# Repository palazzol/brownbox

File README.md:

# Ralph Baer's "Brown Box" prototype

## Ralph Baer created a series of [TV game prototypes](https://americanhistory.si.edu/collections/object-groups/the-father-of-the-video-game-the-ralph-baer-prototypes-and-electronic-games) in the 1960s, that led to the first commercial TV game console, the [Magnavox Odyssey](https://en.wikipedia.org/wiki/Magnavox_Odyssey). This github is for files related to the the ["Brown Box"](https://americanhistory.si.edu/collections/search/object/nmah_1301997) - the last prototype that was created and resides in the Smithsonian.

## Goals
1. We would like to create a **functional PCB version** of the Brown Box, which can be populated by modern (or vintage) transistors

1. We have reason to believe the "build to print" Brown Box, and the actual artifact, are *__somewhat different__*.  We want to understand these differences, as well as the differences between the "brown box" and the eventual manufactured Magnavox Odyssey console.

## Contents

The current KiCAD schematic and PCB layout is based on this original schematic, which is the best copy "available" on the Smithsonian website.

https://raw.githubusercontent.com/palazzol/brownbox/master/original_schems/NMAH-AC0854-0000802.jpg

### The KiCAD schematic is complete!

### The initial KiCAD PCB is finally done!

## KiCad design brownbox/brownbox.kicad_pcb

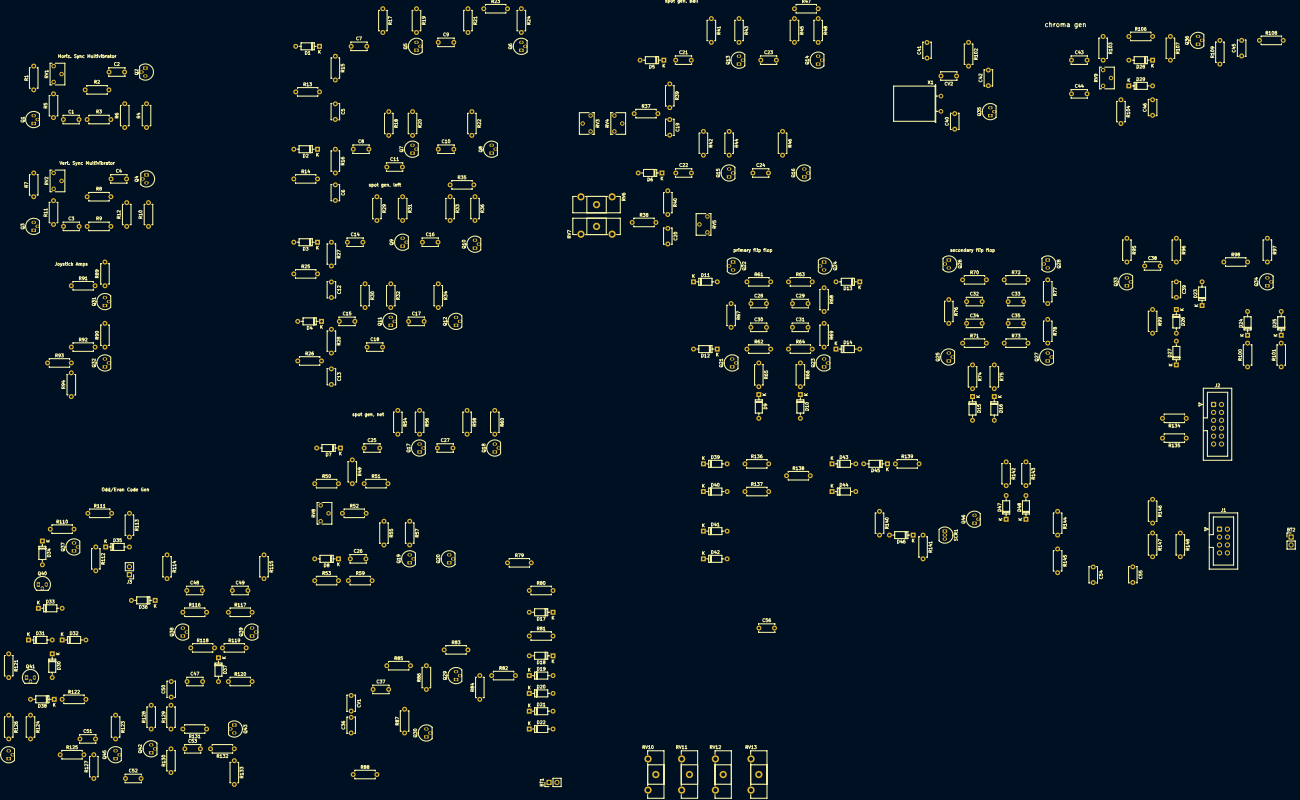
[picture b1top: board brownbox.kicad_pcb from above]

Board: 2 copper layers, 319 parts (0 on the bottom side), 160 nets, no tracks yet.

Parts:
BT1: 4 D Cells; PinHeader_1x02_P2.54mm_Vertical
BT2: 1 C Cell; PinHeader_1x02_P2.54mm_Vertical
C1: 390pF; C_Disc_D5.0mm_W2.5mm_P5.00mm
C2: 330pF; C_Disc_D5.0mm_W2.5mm_P5.00mm
C3, C8, C10, C15, C17, C22, C24, C26, C28, C29, C32, C33, C39, C47, C52, C53: 0.1uF; C_Disc_D5.0mm_W2.5mm_P5.00mm
C4: 0.2uF; C_Disc_D5.0mm_W2.5mm_P5.00mm
C5, C6, C12, C13, C19, C20: 100uF; C_Disc_D5.0mm_W2.5mm_P5.00mm
C7, C14, C21, C25: 750pF; C_Disc_D5.0mm_W2.5mm_P5.00mm
C9, C16, C23, C27: 130pF; C_Disc_D5.0mm_W2.5mm_P5.00mm
C11, C18, C41, C48, C49, C50: 0.01uF; C_Disc_D5.0mm_W2.5mm_P5.00mm
C30, C31, C34, C35: 100pF; C_Disc_D5.0mm_W2.5mm_P5.00mm
C36: 82pF; C_Disc_D5.0mm_W2.5mm_P5.00mm
C37, C43: 180pF; C_Disc_D5.0mm_W2.5mm_P5.00mm
C38: 0.22uF; C_Disc_D5.0mm_W2.5mm_P5.00mm
C40: 27pF; C_Disc_D5.0mm_W2.5mm_P5.00mm
C42: 62pF; C_Disc_D5.0mm_W2.5mm_P5.00mm
C44: 56pF; C_Disc_D5.0mm_W2.5mm_P5.00mm
C45: 360pF; C_Disc_D5.0mm_W2.5mm_P5.00mm
C46: 120pF; C_Disc_D5.0mm_W2.5mm_P5.00mm
C51: 0.3uF; C_Disc_D5.0mm_W2.5mm_P5.00mm
C54, C55: 10uF; C_Disc_D5.0mm_W2.5mm_P5.00mm
C56: 0.02uF; C_Disc_D5.0mm_W2.5mm_P5.00mm
CV1, CV2: 9-35pF; C_Disc_D5.0mm_W2.5mm_P5.00mm
D1, D2, D3, D4, D5, D6, D7, D8, D9, D10, D15, D16, D17, D18, D19, D20, D21, D22, D24, D25, D26, D27, D28, D29, D30, D31, D32, D33, D34, D35, D36, D37, D38, D45, D46, D47, D48: 1N4148; D_DO-35_SOD27_P7.62mm_Horizontal
D11, D12, D13, D14, D23, D39, D40, D41, D42, D43, D44: 1N270; D_DO-35_SOD27_P7.62mm_Horizontal
J1: Rifle Connector - C7-205; IDC-Header_2x04_P2.54mm_Vertical
J2: 12-Pin Cinch Jones Expansion Connector; IDC-Header_2x06_P2.54mm_Vertical
J3: Jumper; PinHeader_1x02_P2.54mm_Vertical
Q1, Q3, Q5, Q6, Q8, Q9, Q10, Q12, Q13, Q14, Q16, Q17, Q18, Q20, Q29, Q30, Q35, Q36: 2N5134; TO-92_Offset_TO-106
Q2, Q4, Q22, Q24, Q26, Q28, Q40, Q41, Q43: 2N5139; TO-92_Offset_TO-106
Q7, Q11, Q15, Q19, Q21, Q23, Q25, Q27, Q31, Q32, Q33, Q34, Q37, Q38, Q39, Q42, Q44, Q45, Q46: 2N5133; TO-92_Offset_TO-106
R1, R2, R3, R4, R7, R8, R9, R10, R13, R14, R23, R25, R26, R35, R37, R38, R47, R67, R76, R85, R131, R132, R133: 2K; R_Axial_DIN0207_L6.3mm_D2.5mm_P7.62mm_Horizontal
R5, R11, R87, R148: 150K; R_Axial_DIN0207_L6.3mm_D2.5mm_P7.62mm_Horizontal
R6, R12: 220K; R_Axial_DIN0207_L6.3mm_D2.5mm_P7.62mm_Horizontal
R15, R16, R19, R20, R24, R27, R28, R31, R32, R36, R39, R40, R43, R44, R48, R49, R53, R56, R57, R60, R65, R66, R74, R75, R83, R86, R93, R95, R97, R103, R104, R110, R111, R114, R115, R120, R123, R126, R134, R135, R139, R140, R141: 10K; R_Axial_DIN0207_L6.3mm_D2.5mm_P7.62mm_Horizontal
R17, R29, R41, R54: 130K; R_Axial_DIN0207_L6.3mm_D2.5mm_P7.62mm_Horizontal
R18, R30, R42, R55: 270K; R_Axial_DIN0207_L6.3mm_D2.5mm_P7.62mm_Horizontal
R21, R33, R45, R122: 33K; R_Axial_DIN0207_L6.3mm_D2.5mm_P7.62mm_Horizontal
R22, R34, R46, R109: 15K; R_Axial_DIN0207_L6.3mm_D2.5mm_P7.62mm_Horizontal
R50, R51, R59, R79, R89, R90, R128, R129, R136, R137, R138: 5.1K; R_Axial_DIN0207_L6.3mm_D2.5mm_P7.62mm_Horizontal
R52: 220; R_Axial_DIN0207_L6.3mm_D2.5mm_P7.62mm_Horizontal
R58, R61, R62, R63, R64, R70, R71, R72, R73, R130, R142, R143: 22K; R_Axial_DIN0207_L6.3mm_D2.5mm_P7.62mm_Horizontal
R68, R69, R77, R78, R144, R145: 1K; R_Axial_DIN0207_L6.3mm_D2.5mm_P7.62mm_Horizontal
R80, R81, R98, R99, R112, R113, R116, R117, R118, R119, R124, R125: 100K; R_Axial_DIN0207_L6.3mm_D2.5mm_P7.62mm_Horizontal
R82, R94: 12K; R_Axial_DIN0207_L6.3mm_D2.5mm_P7.62mm_Horizontal
R84: 1.8K; R_Axial_DIN0207_L6.3mm_D2.5mm_P7.62mm_Horizontal
R88: 270; R_Axial_DIN0207_L6.3mm_D2.5mm_P7.62mm_Horizontal
R91, R92, R108, R121, R127: 51K; R_Axial_DIN0207_L6.3mm_D2.5mm_P7.62mm_Horizontal
R96: 510K; R_Axial_DIN0207_L6.3mm_D2.5mm_P7.62mm_Horizontal
R100, R101: 20K; R_Axial_DIN0207_L6.3mm_D2.5mm_P7.62mm_Horizontal
R102: 300K; R_Axial_DIN0207_L6.3mm_D2.5mm_P7.62mm_Horizontal
R106, R107: 6.2K; R_Axial_DIN0207_L6.3mm_D2.5mm_P7.62mm_Horizontal
R146, R147: 100; R_Axial_DIN0207_L6.3mm_D2.5mm_P7.62mm_Horizontal
RV1, RV2: 100K; Potentiometer_Bourns_3266W_Vertical
RV3, RV5, RV8: 10K; Potentiometer_Bourns_3266W_Vertical
RV4, RV9: 5K; Potentiometer_Bourns_3266W_Vertical
RV6, RV7: 25K; Potentiometer_Piher_PT-15-H01_Horizontal
RV10, RV11, RV12, RV13: 5K; Potentiometer_Piher_PT-15-H01_Horizontal
SCR1: NT854; TO-92_Inline
X1: 3.579545Mhz; Crystal_HC49-U_Horizontal

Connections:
A: D17.1 (K), Q1.3 (C), R1.1, R2.2, R80.2, R108.2
B: D18.1 (K), Q3.3 (C), R7.1, R8.2, R81.2
E: C31.1, Q21.2 (B), R64.1, R65.1, R100.1
E': C35.1, Q25.2 (B), R73.1, R74.1, R75.1
F: C30.2, Q23.2 (B), R62.2, R66.1, R101.1
F': C34.2, Q27.2 (B), R71.2
GNDREF: BT1.2 (-), C5.2, C6.2, C12.2, C13.2, C19.2, C20.2, C36.2, C40.1, C41.1, C45.1, C54.2, C55.2, CV1.2, Q1.1 (E), Q3.1 (E), Q5.1 (E), Q6.1 (E), Q7.1 (E), Q8.1 (E), Q9.1 (E), Q10.1 (E), Q11.1 (E), Q12.1 (E), Q13.1 (E), Q14.1 (E), Q15.1 (E), Q16.1 (E), Q17.1 (E), Q18.1 (E), Q19.1 (E), Q20.1 (E), Q21.1 (E), Q23.1 (E), Q25.1 (E), Q27.1 (E), Q29.1 (E), Q30.1 (E), Q31.1 (E), Q32.1 (E), Q33.1 (E), Q34.1 (E), Q35.1 (E), Q36.1 (E), Q37.1 (E), Q38.1 (E), Q39.1 (E), Q42.1 (E), Q44.1 (E), Q45.1 (E), Q46.1 (E), R4.2, R6.2, R10.2, R12.2, R50.1, R53.1, R84.1, R94.2, R99.2, R104.2, R109.1, R112.2, R120.2, R130.1, R133.2, R141.2, R145.2, R148.2, RV3.1, RV5.1, RV8.3, RV10.3, RV11.3, RV12.3, RV13.3, SCR1.3 (K)
unnamed: C1.1, Q1.2 (B), R5.2
unnamed: C1.2, R3.2
unnamed: C2.1, Q2.2 (B), R6.1
unnamed: C2.2, R2.1
unnamed: C3.1, Q3.2 (B), R11.2
unnamed: C3.2, R9.2
unnamed: C4.1, Q4.2 (B), R12.1
unnamed: C4.2, R8.1
unnamed: C5.1, R13.2, R15.2
unnamed: C6.1, R14.2, R16.2
unnamed: C7.1, D1.1 (K), R15.1
unnamed: C7.2, Q5.2 (B), R17.2
unnamed: C8.2, Q7.2 (B), R18.2
unnamed: C9.1, Q5.3 (C), R19.2
unnamed: C9.2, Q6.2 (B), R21.2
unnamed: C10.1, Q7.3 (C), R20.2
unnamed: C10.2, C11.2, Q8.2 (B), R22.2
unnamed: C8.1, C11.1, D2.1 (K), R16.1
unnamed: C12.1, R25.2, R27.2
unnamed: C13.1, R26.2, R28.2
unnamed: C14.1, D3.1 (K), R27.1
unnamed: C14.2, Q9.2 (B), R29.2
unnamed: C15.1, C18.1, D4.1 (K), R28.1
unnamed: C15.2, Q11.2 (B), R30.2
unnamed: C16.1, Q9.3 (C), R31.2
unnamed: C16.2, Q10.2 (B), R33.2
unnamed: C17.1, Q11.3 (C), R32.2
unnamed: C17.2, C18.2, Q12.2 (B), R34.2
unnamed: C19.1, R37.2, R39.2
unnamed: C20.1, R38.2, R40.2
unnamed: C21.2, Q13.2 (B), R41.2
unnamed: C22.2, Q15.2 (B), R42.2
unnamed: C23.1, Q13.3 (C), R43.2
unnamed: C23.2, Q14.2 (B), R45.2
unnamed: C24.1, Q15.3 (C), R44.2
unnamed: C24.2, Q16.2 (B), R46.2
unnamed: C25.1, D7.1 (K), R49.1
unnamed: C25.2, Q17.2 (B), R54.2
unnamed: C26.1, D8.1 (K), R53.2, R59.1
unnamed: C26.2, Q19.2 (B), R55.2
unnamed: C27.1, Q17.3 (C), R56.2
unnamed: C27.2, Q18.2 (B), R58.2
unnamed: C28.1, D11.2 (A), Q22.3 (C), R61.1, R67.1
unnamed: C28.2, Q24.2 (B), R61.2
unnamed: C29.1, Q22.2 (B), R63.1
unnamed: C29.2, D13.2 (A), Q24.3 (C), R63.2, R68.1
unnamed: C30.1, D12.1 (K), Q21.3 (C), R62.1, R67.2
unnamed: C31.2, D14.1 (K), Q23.3 (C), R64.2, R69.2
unnamed: C32.1, Q26.3 (C), R70.1, R76.1
unnamed: C32.2, Q28.2 (B), R70.2
unnamed: C33.1, Q26.2 (B), R72.1
unnamed: C33.2, Q28.3 (C), R72.2, R77.1
unnamed: C34.1, Q25.3 (C), R71.1, R76.2
unnamed: C35.2, Q27.3 (C), R73.2, R78.2
unnamed: C36.1, Q30.2 (B), R87.1
unnamed: C37.1, CV1.1
unnamed: C37.2, Q30.3 (C), R86.1, R87.2
unnamed: C38.1, Q33.3 (C), R95.2
unnamed: C38.2, D23.2 (A), Q34.2 (B), R96.2
unnamed: C39.1, Q33.2 (B), R98.1
unnamed: C39.2, D26.1 (K), R99.1
unnamed: C40.2, Q35.2 (B), R102.2, X1.2
unnamed: C42.1, CV2.1, Q35.3 (C)
unnamed: C43.2, D28.2 (A), R103.2, R104.1, RV9.1
unnamed: C44.2, D29.1 (K), RV9.2, RV9.3
unnamed: C45.2, Q36.2 (B), R108.1, R109.2
unnamed: C46.2, D28.1 (K), D29.2 (A), R107.2
unnamed: C47.1, C50.2, D33.2 (A), Q40.3 (C)
unnamed: C47.2, D37.2 (A), R120.1
unnamed: C48.1, D36.1 (K), Q38.3 (C), R114.2, R116.1
unnamed: C48.2, Q39.2 (B), R116.2, R119.2
unnamed: C49.1, Q38.2 (B), R117.1, R118.1
unnamed: C49.2, C52.2, Q39.3 (C), R115.2, R117.2
unnamed: C50.1, R129.2
unnamed: C51.1, Q44.2 (B)
unnamed: C51.2, Q45.3 (C), R122.2, R123.2
unnamed: C52.1, R127.1
unnamed: C53.1, Q42.2 (B), R129.1, R130.2
unnamed: C53.2, R132.2
unnamed: CV2.2, X1.1
unnamed: D1.2 (A), D3.2 (A), D5.2 (A), D7.2 (A), Q2.3 (C), R3.1, R4.1
unnamed: D9.1 (K), R65.2
unnamed: D10.1 (K), R66.2
unnamed: D15.1 (K), R74.2
unnamed: D16.1 (K), R75.2
unnamed: D17.2 (A), D18.2 (A), D19.1 (K), D20.1 (K), D21.1 (K), D22.1 (K), R82.2
unnamed: D21.2 (A), D42.1 (K), Q10.3 (C), Q12.3 (C), R36.2
unnamed: D22.2 (A), D41.1 (K), Q6.3 (C), Q8.3 (C), R24.2
unnamed: D24.1 (K), R100.2
unnamed: D24.2 (A), D25.2 (A), Q34.3 (C), R97.2, R98.2
unnamed: D25.1 (K), R101.2
unnamed: D30.2 (A), Q41.3 (C)
unnamed: D34.1 (K), R110.1
unnamed: D34.2 (A), Q40.2 (B)
unnamed: D35.1 (K), Q37.2 (B), R112.1
unnamed: D35.2 (A), J3.2, R113.2
unnamed: D36.2 (A), J3.1
unnamed: D37.1 (K), R118.2, R119.1
unnamed: D38.1 (K), R122.1
unnamed: D38.2 (A), Q41.2 (B), R121.2
unnamed: D43.2 (A), D44.2 (A), D45.2 (A), R138.2
unnamed: D45.1 (K), R139.1
unnamed: D47.1 (K), D48.1 (K), Q46.2 (B)
unnamed: D47.2 (A), R142.2
unnamed: D48.2 (A), R143.2
unnamed: Q19.3 (C), Q20.2 (B), R57.2
unnamed: Q29.2 (B), R79.1, R80.1, R81.1, R82.1, R83.2, R84.2
unnamed: Q29.3 (C), R83.1, R85.2, R86.2
unnamed: Q32.2 (B), R92.1, R93.2, R94.1
unnamed: Q36.3 (C), R106.2, R107.1
unnamed: Q37.3 (C), R110.2, R111.1
unnamed: Q42.3 (C), R128.1, R131.2
unnamed: Q43.2 (B), R131.1
unnamed: Q44.3 (C), R124.2, R125.1, R126.2
unnamed: Q45.2 (B), R125.2, R127.2
unnamed: R5.1, RV1.2, RV1.3
unnamed: R11.1, RV2.2, RV2.3
unnamed: R23.2, R24.1
unnamed: R52.1, RV8.2
S: C46.1, R79.2
S1A2: R47.2, R48.1
S1A3: R35.2, R36.1
S1B2: D19.2 (A), D44.1 (K), Q18.3 (C), R60.2
S2A3: Q31.3 (C), R89.2, R91.2
S2B3: Q32.3 (C), R90.2, R92.2
S2C2: C56.1, D26.2 (A), D27.1 (K), D27.2 (A), D46.1 (K), R141.1, SCR1.2 (G)
S2D2: Q46.3 (C), SCR1.1 (A)
S2D3: D23.1 (K), Q31.2 (B), R91.1
S3A3: D20.2 (A), D39.1 (K), D40.1 (K), D43.1 (K), Q14.3 (C), Q16.3 (C), R48.2
S4A3: R146.2, R147.1, R148.1
S7B2: RV6.2, RV7.2
S8A2: D9.2 (A), D15.2 (A), D40.2 (A), R137.1
S8A3: D46.2 (A), R140.2
S8B2: D10.2 (A), D16.2 (A), D39.2 (A), R136.1
S9A2: Q26.1 (E), Q28.1 (E)
S9B1: RV4.2, RV4.3
S9B2: R77.2, R78.1
S9B3: R68.2, R69.1
S9D1: R49.2, R50.2, R51.1
S11A3: Q43.1 (E), R111.2, R113.1, R114.1, R115.1, R123.1, R124.1, R126.1, R128.2
S11B3: D31.1 (K), D33.1 (K), Q40.1 (E), Q41.1 (E), R121.1
S11C1: D4.2 (A), D6.2 (A), D8.2 (A)
S11C2: Q4.3 (C), R9.1, R10.1
S11C3: D32.2 (A), Q43.3 (C), R132.1, R133.1
S11D3: D30.1 (K), D31.2 (A), D32.1 (K)
S12A3: C41.2, C42.2, R102.1, R103.1, R106.1
S16A1: C21.1, D5.1 (K)
S16B1: C22.1, D6.1 (K)
VCC: Q2.1 (E), Q4.1 (E), Q22.1 (E), Q24.1 (E), R1.2, R7.2, R17.1, R18.1, R19.1, R20.1, R21.1, R22.1, R23.1, R29.1, R30.1, R31.1, R32.1, R33.1, R34.1, R35.1, R41.1, R42.1, R43.1, R44.1, R45.1, R46.1, R47.1, R51.2, R54.1, R55.1, R56.1, R57.1, R58.1, R59.2, R60.1, R85.1, R89.1, R90.1, R95.1, R96.1, R97.1, R136.2, R137.2, R138.1, R142.1, R143.1, R144.1, RV1.1, RV2.1, RV3.3, RV5.3, RV8.1, RV10.1, RV11.1, RV12.1, RV13.1
a: D11.1 (K), RV6.3
b: D12.2 (A), RV7.1
c: D13.1 (K), RV7.3
d: D14.2 (A), RV6.1

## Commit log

2021-01-25 Add .gitignore first for KiCad project
2021-01-26 All parts placed, values verified
2021-01-26 Update PDF
2021-01-27 Update RefDes's
2021-01-27 A few more Refdes's
2021-01-27 Fix duplicate Refdes - annotation complete
2021-01-27 Flip D12
2021-01-27 Flip D23
2021-01-27 More small fixes
2021-01-27 Placed NCs, more fixes, Electrical Rules Check makes sense now
2021-01-28 Start adding footprints
2022-07-16 need to review these updates
2022-07-16 Update to kicad6
2022-07-16 Remove backup dir
2022-07-16 Add .gitignore
2022-07-16 Remove this file from version control
2022-07-16 Update separate osc project to kicad6
2022-07-16 Temp remove .gitignore again
2022-07-16 Remove kicad5 and temp files
2022-07-16 Re-add .gitignore
2022-07-17 Remove redundant backup directory
2022-07-17 Consolidate spice files into spice directory
2022-07-23 Migrate symbol libraries to 6.0 format
2022-07-23 Remove kicad5 stuff
2022-07-23 Remove some old SPICE stuff
2022-07-23 Move .gitignore
2022-07-23 Update empty pcb file
2022-07-23 Add additional pics from the Smithsonian
2022-07-23 Add some additional spice files
2022-07-23 Add additional PDF, references to papers
2022-07-24 Update BJTs with TO-92/TO-106 compatible footprints
2022-07-25 capacitor footprints picked and some layout started
2022-07-25 more layout
2022-08-01 more preliminary layout
2022-08-08 still working on placement
2022-08-09 finished initial placement
2023-04-21 routed board without buttons
2023-12-17 finished layout
2024-01-18 added pictures
2024-04-02 updated pcb for fab
2024-07-28 adjusted some positions
